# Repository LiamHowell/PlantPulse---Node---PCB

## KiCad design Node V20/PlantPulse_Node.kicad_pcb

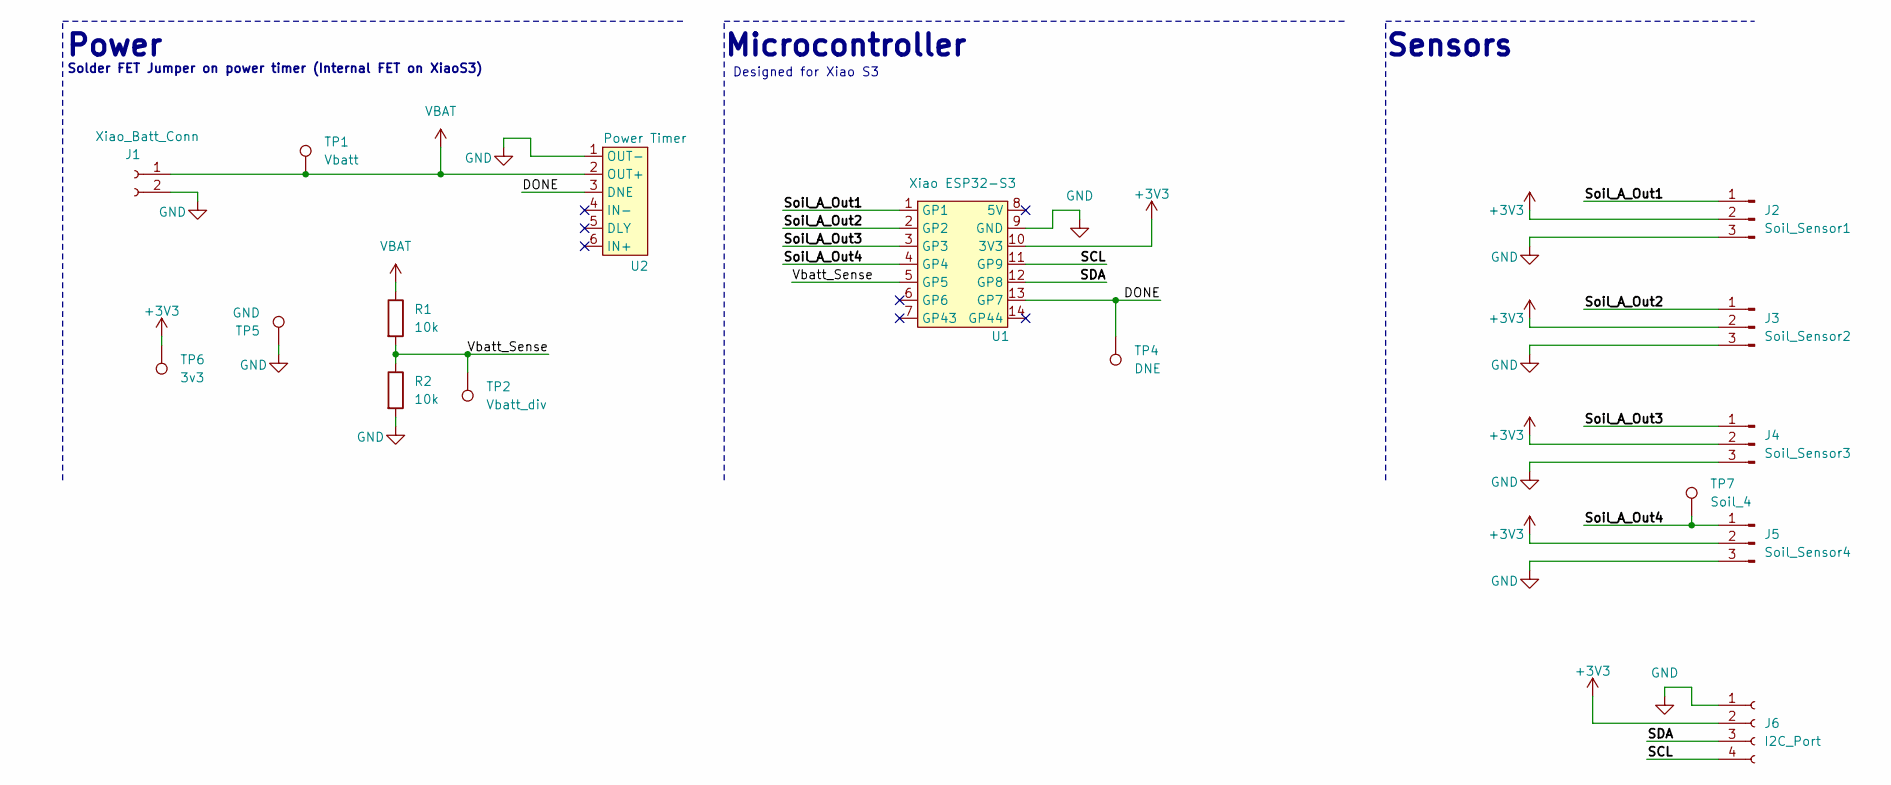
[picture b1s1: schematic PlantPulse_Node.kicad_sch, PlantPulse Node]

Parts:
J1: Xiao_Batt_Conn; PinSocket_1x02_P2.54mm_Horizontal
J2: Soil_Sensor1; PinHeader_1x03_P2.54mm_Vertical
J3: Soil_Sensor2; PinHeader_1x03_P2.54mm_Vertical
J4: Soil_Sensor3; PinHeader_1x03_P2.54mm_Vertical
J5: Soil_Sensor4; PinHeader_1x03_P2.54mm_Vertical
J6: I2C_Port; PinSocket_1x04_P2.54mm_Vertical
R1, R2: 10k; R_Axial_DIN0207_L6.3mm_D2.5mm_P7.62mm_Horizontal
TP1: Vbatt; TestPoint_THTPad_D1.5mm_Drill0.7mm
TP2: Vbatt_div; TestPoint_THTPad_D1.5mm_Drill0.7mm
TP4: DNE; TestPoint_THTPad_D1.5mm_Drill0.7mm
TP5: GND; TestPoint_THTPad_D1.5mm_Drill0.7mm
TP6: 3v3; TestPoint_THTPad_D1.5mm_Drill0.7mm
TP7: Soil_4; TestPoint_THTPad_D1.5mm_Drill0.7mm
U1: Xiao ESP32-S3; Xiao-S3
U2: Power Timer; Nano Power Timer

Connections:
+3V3: J2.2, J3.2, J4.2, J5.2, J6.2, TP6.1, U1.10 (3V3)
/DONE: TP4.1, U1.13 (GP7), U2.3 (DNE)
/SCL: J6.4, U1.11 (GP9)
/SDA: J6.3, U1.12 (GP8)
/Soil_A_Out1: J2.1, U1.1 (GP1)
/Soil_A_Out2: J3.1, U1.2 (GP2)
/Soil_A_Out3: J4.1, U1.3 (GP3)
/Soil_A_Out4: J5.1, TP7.1, U1.4 (GP4)
/Vbatt_Sense: R1.2, R2.1, TP2.1, U1.5 (GP5)
GND: J1.2, J2.3, J3.3, J4.3, J5.3, J6.1, R2.2, TP5.1, U1.9 (GND), U2.1 (OUT-)
VBAT: J1.1, R1.1, TP1.1, U2.2 (OUT+)

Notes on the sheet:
Power
Microcontroller
Solder FET Jumper on power timer (Internal FET on XiaoS3)
Sensors
Designed for Xiao S3

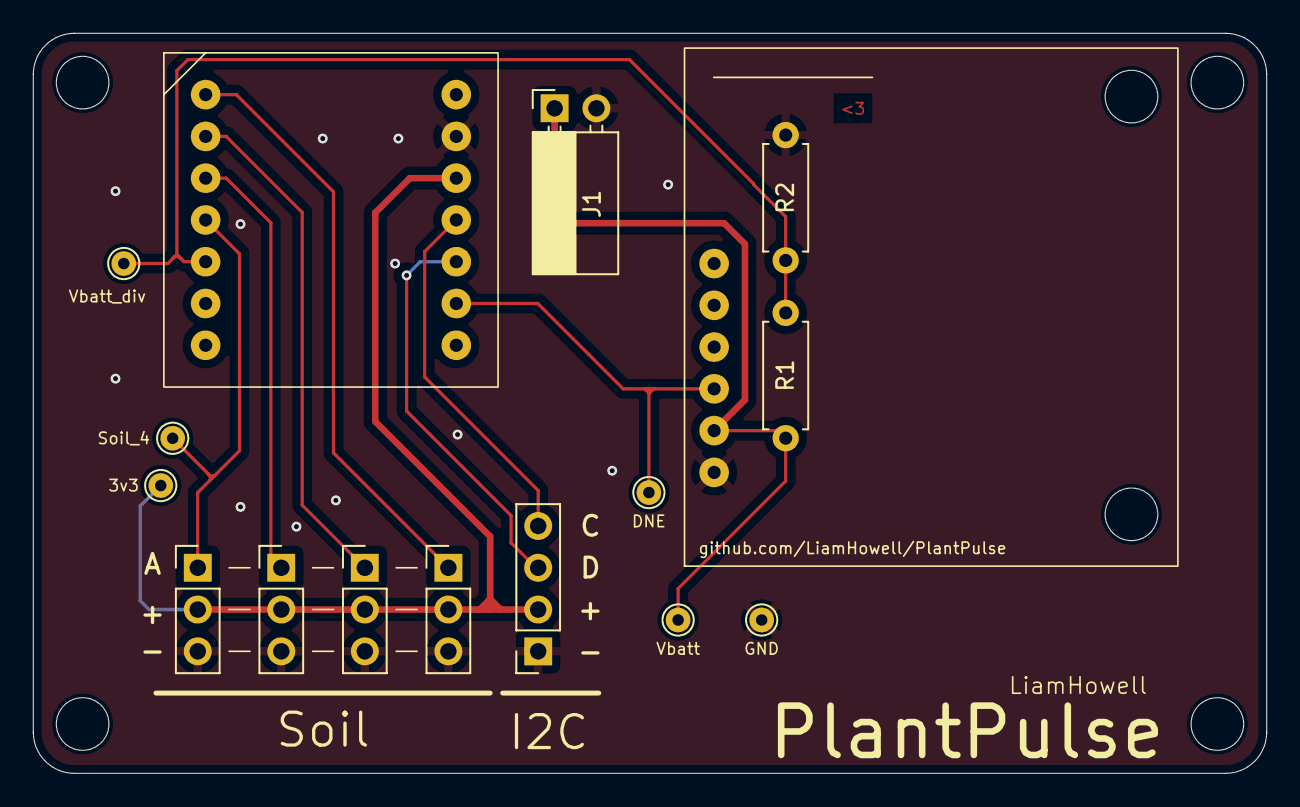
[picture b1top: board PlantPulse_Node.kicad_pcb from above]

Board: 2 copper layers, 75.0 x 45.0 mm, 16 parts (0 on the bottom side), 11 nets.

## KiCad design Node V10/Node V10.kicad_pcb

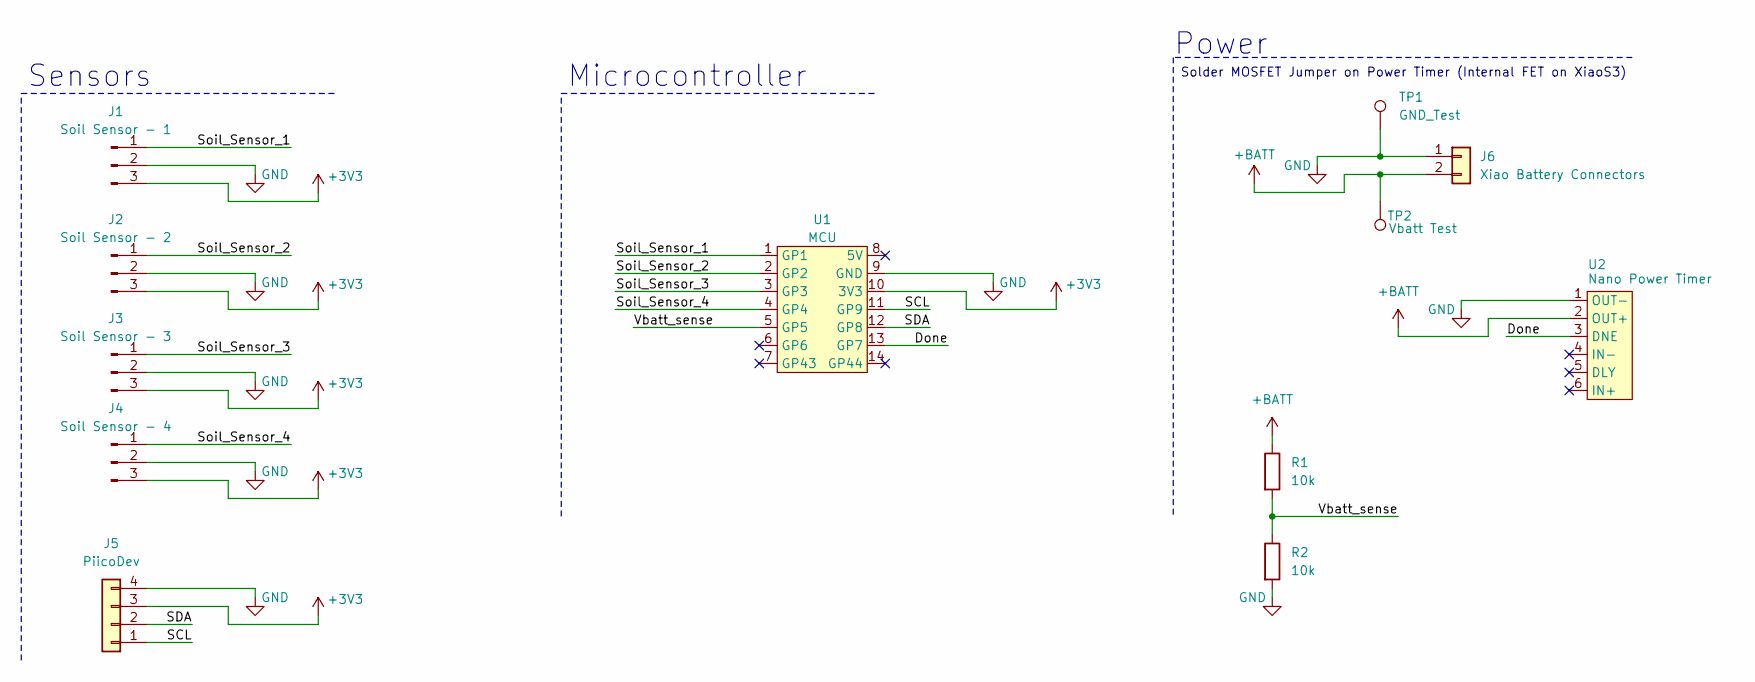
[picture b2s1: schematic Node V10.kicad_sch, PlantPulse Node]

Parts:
J1: Soil Sensor - 1; PinHeader_1x03_P2.54mm_Vertical
J2: Soil Sensor - 2; PinHeader_1x03_P2.54mm_Vertical
J3: Soil Sensor - 3; PinHeader_1x03_P2.54mm_Vertical
J4: Soil Sensor - 4; PinHeader_1x03_P2.54mm_Vertical
J5: PiicoDev; PiicoDev Breadboard
J6: Xiao Battery Connectors; PinHeader_1x02_P2.54mm_Horizontal
R1, R2: 10k; R_Axial_DIN0207_L6.3mm_D2.5mm_P7.62mm_Horizontal
TP1: GND_Test; TestPoint_THTPad_1.0x1.0mm_Drill0.5mm
TP2: Vbatt Test; TestPoint_THTPad_1.0x1.0mm_Drill0.5mm
U1: MCU; Xiao-S3
U2: Nano Power Timer

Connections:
+3V3: J1.3, J2.3, J3.3, J4.3, J5.3, U1.10 (3V3)
+BATT: J6.2, R1.1, TP2.1, U2.2 (OUT+)
/Done: U1.13 (GP7), U2.3 (DNE)
/SCL: J5.1, U1.11 (GP9)
/SDA: J5.2, U1.12 (GP8)
/Soil_Sensor_1: J1.1, U1.1 (GP1)
/Soil_Sensor_2: J2.1, U1.2 (GP2)
/Soil_Sensor_3: J3.1, U1.3 (GP3)
/Soil_Sensor_4: J4.1, U1.4 (GP4)
/Vbatt_sense: R1.2, R2.1, U1.5 (GP5)
GND: J1.2, J2.2, J3.2, J4.2, J5.4, J6.1, R2.2, TP1.1, U1.9 (GND), U2.1 (OUT-)

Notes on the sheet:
Microcontroller
Solder MOSFET Jumper on Power Timer (Internal FET on XiaoS3)
Sensors
Power

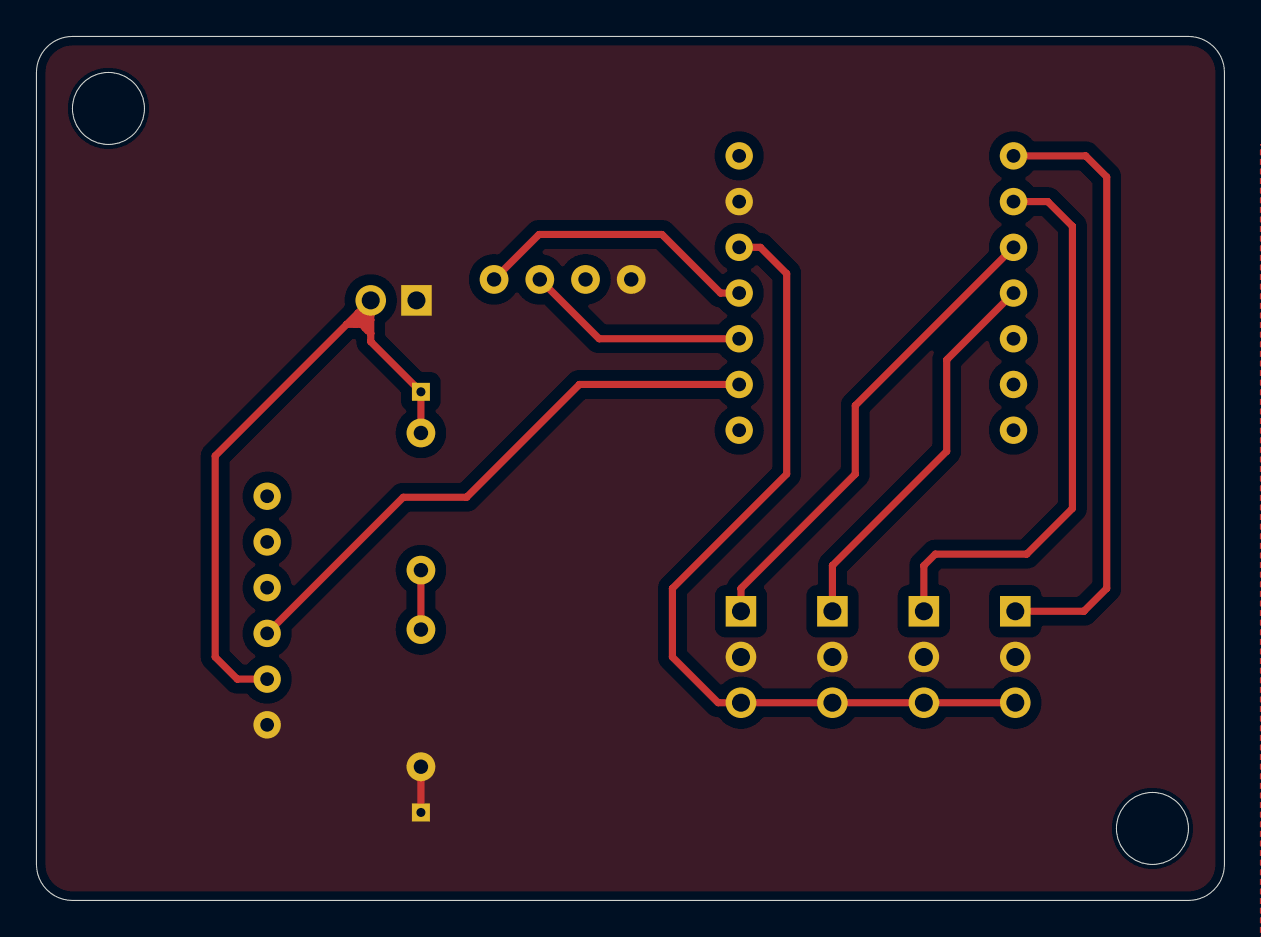
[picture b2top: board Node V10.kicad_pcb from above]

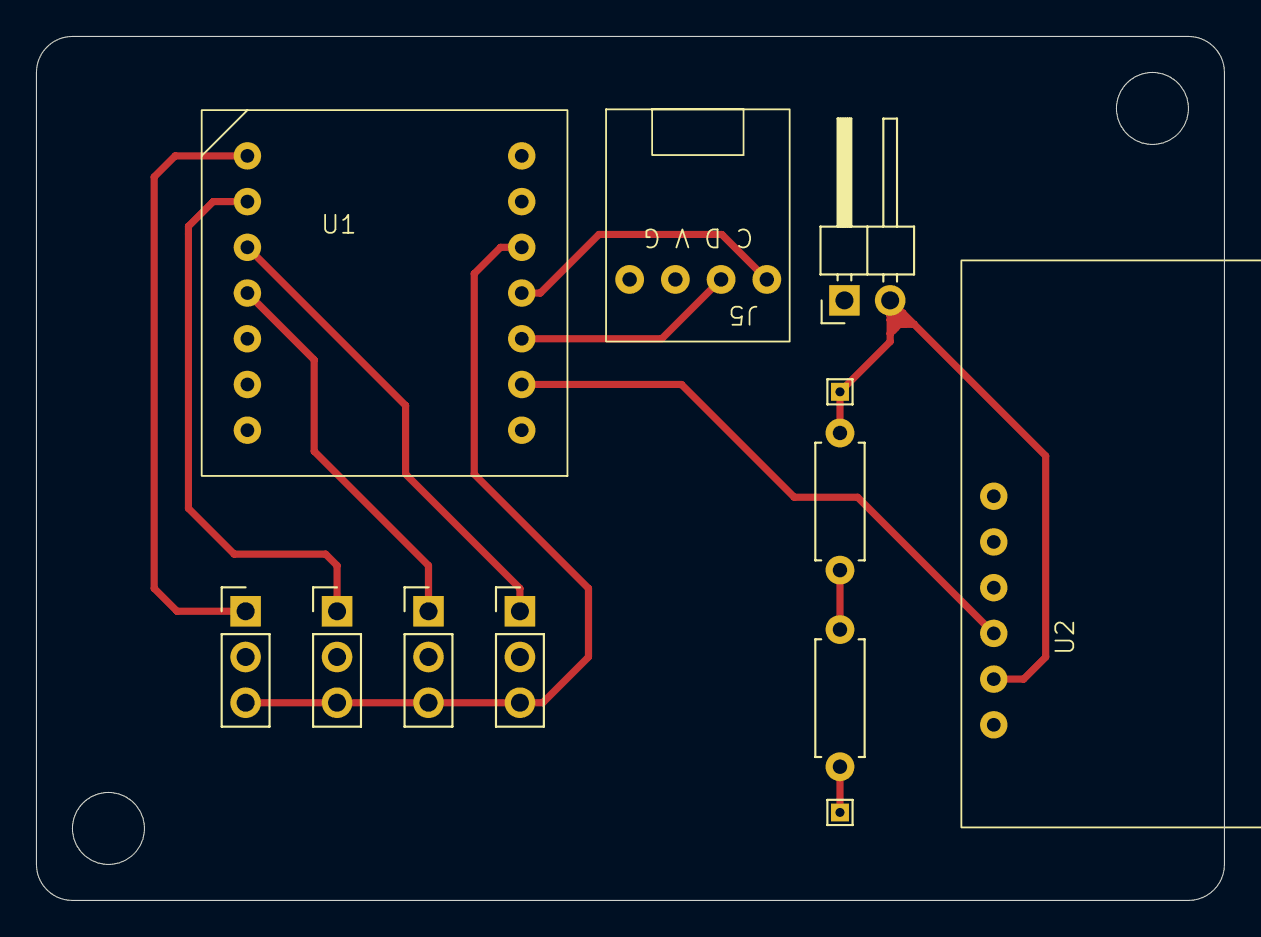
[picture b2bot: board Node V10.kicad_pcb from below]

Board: 2 copper layers, 66.0 x 48.0 mm, 12 parts (12 on the bottom side), 11 nets.

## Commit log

2024-03-04 Working on PCB
2024-03-04 Completed schamtic
2024-03-04 Footprints assigned
2024-03-04 There are 14 pins oops
2024-03-12 Ready for fab (flip to front)
2024-03-13 Additions
2024-05-07 PCB for fab
2024-05-07 Moved to correct location
